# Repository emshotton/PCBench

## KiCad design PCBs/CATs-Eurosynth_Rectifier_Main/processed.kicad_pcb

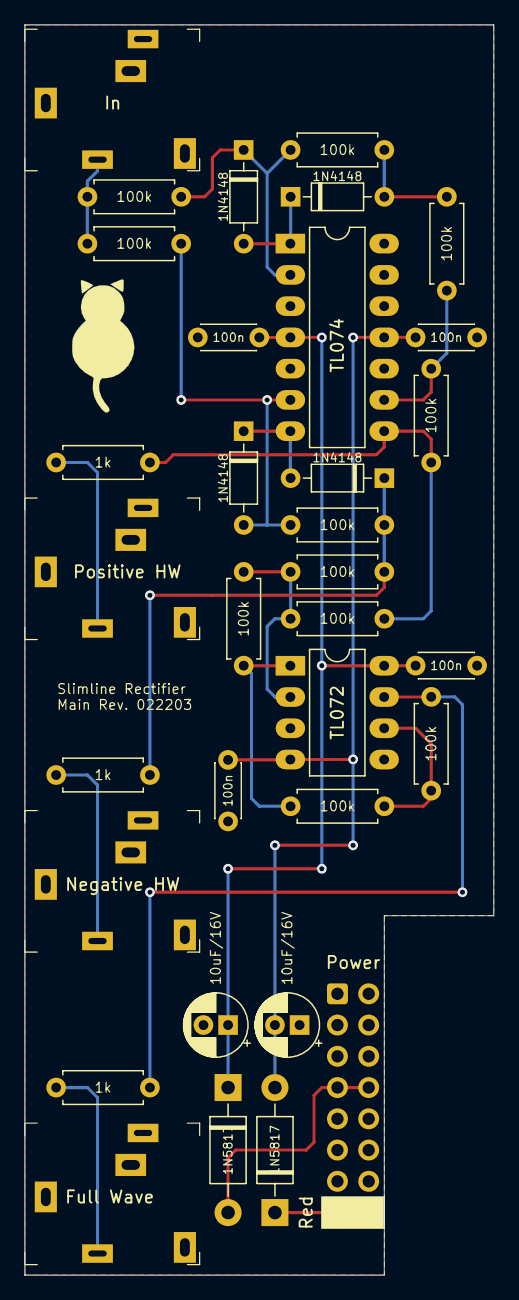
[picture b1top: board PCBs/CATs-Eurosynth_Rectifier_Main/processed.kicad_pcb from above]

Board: 2 copper layers, 38.1 x 101.6 mm, 33 parts (0 on the bottom side), 21 nets.

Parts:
C1, C4: 10uF/16V; CP_Radial_D5.0mm_P2.00mm
C2, C3, C5, C6: 100n; C_Disc_D4.3mm_W1.9mm_P5.00mm
D1, D2, D3, D4: 1N4148; D_DO-35_SOD27_P7.62mm_Horizontal
D5, D6: 1N5817; D_DO-41_SOD81_P10.16mm_Horizontal
J1: Negative HW; Jack_3.5mm_QingPu_WQP-PJ324M
J2: Full Wave; Jack_3.5mm_QingPu_WQP-PJ324M
J3: In; Jack_3.5mm_QingPu_WQP-PJ324M
J4: Positive HW; Jack_3.5mm_QingPu_WQP-PJ324M
J5: Power; Power_2x8_Horizontal
R1, R3, R4, R5, R6, R7, R8, R10, R11, R12, R13: 100k; R_Axial_DIN0207_L6.3mm_D2.5mm_P7.62mm_Horizontal
R2, R9, R14: 1k; R_Axial_DIN0207_L6.3mm_D2.5mm_P7.62mm_Horizontal
U1: TL074; DIP-14_W7.62mm_LongPads
U2: TL072; DIP-8_W7.62mm_LongPads

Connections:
+12V: C1.1, C2.1, C6.2, D5.1 (K), U1.4 (V+), U2.8 (V+)
-12V: C3.1, C4.2, C5.2, D6.2 (A), U1.11 (V-), U2.4 (V-)
GND: C1.2, C2.2, C3.2, C4.1, C5.1, C6.1, J1.S, J2.S, J3.S, J3.TN, J4.S, J5.GND, U1.3 (+), U1.5 (+), U1.10 (+), U2.3 (+), U2.5 (+)
unnamed: D1.1 (K), D2.2 (A), U1.7
unnamed: D1.2 (A), R1.1, R3.2, U1.6 (-)
unnamed: D2.1 (K), R1.2, R2.1, R5.1
unnamed: D3.1 (K), R10.1, R12.2, U1.2 (-)
unnamed: D3.2 (A), D4.1 (K), U1.1
unnamed: D4.2 (A), R10.2, R13.1
unnamed: D5.2 (A), J5.+12V
unnamed: D6.1 (K), J5.-12V
unnamed: J1.T, R2.2
unnamed: J2.T, R9.2
unnamed: J3.T, R3.1, R12.1
unnamed: J4.T, R14.2
unnamed: R4.1, R8.2, U2.6 (-)
unnamed: R4.2, R9.1, U2.7
unnamed: R5.2, R6.1, R7.2, U2.2 (-)
unnamed: R6.2, R8.1, U2.1
unnamed: R11.1, R13.2, U1.9 (-)
unnamed: R7.1, R11.2, R14.1, U1.8

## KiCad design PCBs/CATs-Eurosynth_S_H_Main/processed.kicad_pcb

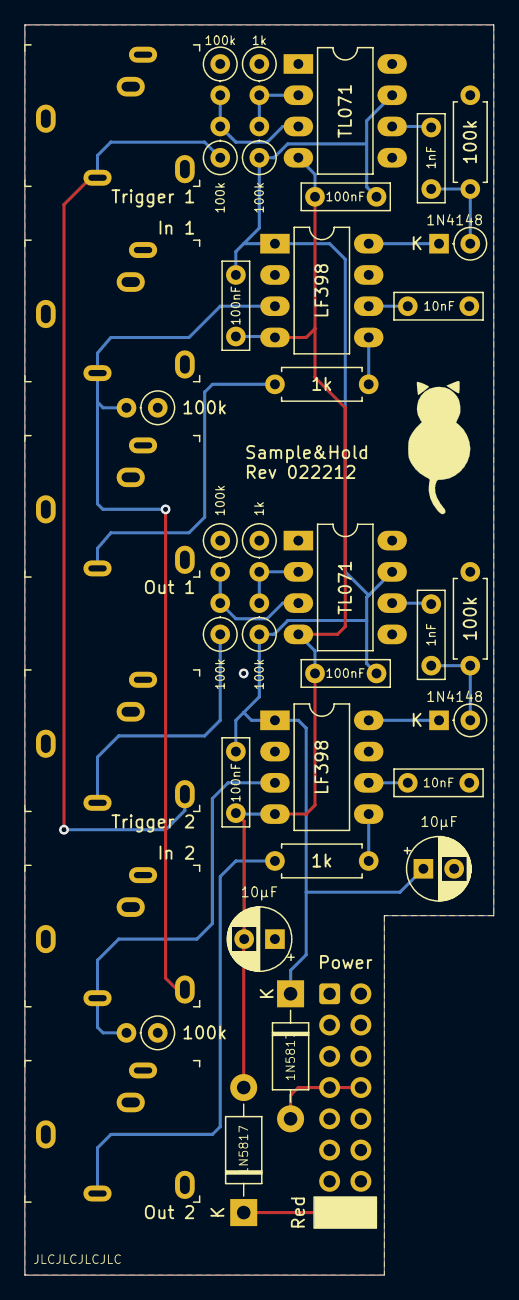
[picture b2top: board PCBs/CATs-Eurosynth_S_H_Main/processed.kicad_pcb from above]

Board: 2 copper layers, 38.1 x 101.6 mm, 39 parts (0 on the bottom side), 25 nets.

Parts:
C1, C2: 1nF; C_Rect_L7.0mm_W2.0mm_P5.00mm
C3, C8, C9, C10: 100nF; C_Rect_L7.0mm_W2.0mm_P5.00mm
C4, C5: 10µF; CP_Radial_D5.0mm_P2.50mm
C6, C7: 10nF; C_Rect_L7.0mm_W2.0mm_P5.00mm
D1, D2: 1N4148; D_DO-35_SOD27_P2.54mm_Vertical_KathodeUp
D3, D4: 1N5817; D_DO-41_SOD81_P10.16mm_Horizontal
J1: Trigger 2; PJ-324M-3
J2: In 2; PJ-324M-3
J3: Trigger 1; PJ-324M-3
J4: In 1; PJ-324M-3
J5: Power; Power_2x8_Horizontal
J6: Out 2; PJ-324M-3
J7: Out 1; PJ-324M-3
R1, R2, R3, R4, R5, R6, R7, R9: 100k; R_Axial_DIN0207_L6.3mm_D2.5mm_P2.54mm_Vertical
R8, R10: 1k; R_Axial_DIN0207_L6.3mm_D2.5mm_P2.54mm_Vertical
R11, R12: 100k; R_Axial_DIN0207_L6.3mm_D2.5mm_P7.62mm_Horizontal
R13, R14: 1k; R_Axial_DIN0207_L6.3mm_D2.5mm_P7.62mm_Horizontal
U1, U4: TL071; DIP-8_W7.62mm_LongPads
U2, U3: LF398; DIP-8_W7.62mm_LongPads

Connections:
+12V: C3.1, C4.1, C8.1, C9.1, C10.1, D3.1, R7.1, R9.1, U1.7, U2.1, U3.1, U4.7
-12V: C3.2, C5.2, C8.2, C9.2, C10.2, D4.2, U1.4, U2.4, U3.4, U4.4
GND: C4.2, C5.1, C6.2, C7.2, J1.S, J2.S, J3.S, J3.TN, J4.S, J4.TN, J5.GND, J6.S, J7.S, R1.1, R2.1, R5.1, R6.1, R8.1, R10.1, R11.1, R12.1, U2.7, U3.7
unnamed: C1.1, D1.2, R11.2
unnamed: C1.2, U1.6
unnamed: C2.1, D2.2, R12.2
unnamed: C2.2, U4.6
unnamed: C6.1, U2.6
unnamed: C7.1, U3.6
unnamed: D1.1, U2.8
unnamed: D2.1, U3.8
unnamed: D3.2, J5.+12V
unnamed: D4.1, J5.-12V
unnamed: J1.T, R3.1
unnamed: J1.TN, J3.T, R4.1
unnamed: J2.T, R1.2, U2.3
unnamed: J2.TN, J4.T, R2.2, U3.3
unnamed: J6.T, R13.1
unnamed: J7.T, R14.1
unnamed: R3.2, R5.2, U1.3
unnamed: R4.2, R6.2, U4.3
unnamed: R7.2, R8.2, U1.2
unnamed: R9.2, R10.2, U4.2
unnamed: R13.2, U2.5
unnamed: R14.2, U3.5

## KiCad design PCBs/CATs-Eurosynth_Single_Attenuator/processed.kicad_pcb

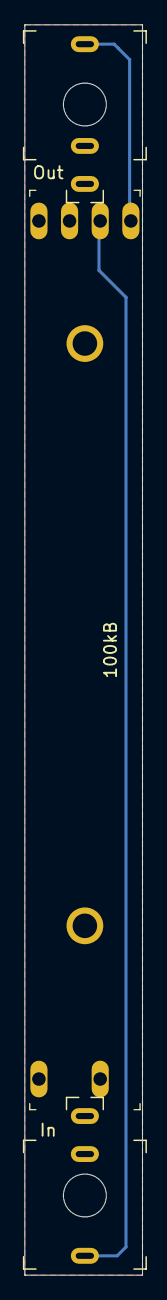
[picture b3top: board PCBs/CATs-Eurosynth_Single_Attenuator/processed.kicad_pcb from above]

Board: 2 copper layers, 9.6 x 102.0 mm, 3 parts (0 on the bottom side), 3 nets.

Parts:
J1: In; PJ-301-M-12
J2: Out; PJ-301-M-12
RV1: 100kB; Potentiometer_Fader_Alps_RS__01_Dual

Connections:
GND: J1.S, J1.TN, J2.S, RV1.3
unnamed: J1.T, RV1.1
unnamed: J2.T, RV1.2

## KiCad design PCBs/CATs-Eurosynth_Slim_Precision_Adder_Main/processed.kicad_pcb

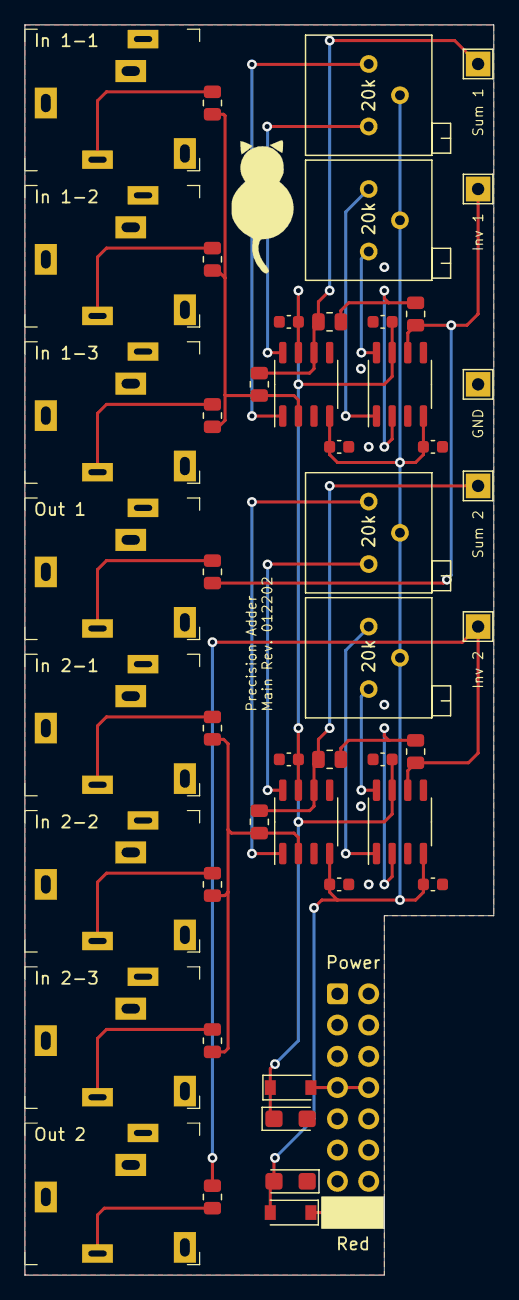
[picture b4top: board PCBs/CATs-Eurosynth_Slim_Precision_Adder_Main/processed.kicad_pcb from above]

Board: 2 copper layers, 38.1 x 101.6 mm, 48 parts (0 on the bottom side), 29 nets.

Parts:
C1, C6: 10u; CP_EIA-3216-18_Kemet-A
C2, C3, C4, C5, C7, C8, C9, C10: 100n; C_0603_1608Metric
D1, D2: B5819W SL; D_SOD-123
J1: In 1-1; Jack_3.5mm_QingPu_WQP-PJ324M
J2: Out 1; Jack_3.5mm_QingPu_WQP-PJ324M
J3: In 1-2; Jack_3.5mm_QingPu_WQP-PJ324M
J4: In 1-3; Jack_3.5mm_QingPu_WQP-PJ324M
J5: In 2-1; Jack_3.5mm_QingPu_WQP-PJ324M
J6: Out 2; Jack_3.5mm_QingPu_WQP-PJ324M
J7: In 2-2; Jack_3.5mm_QingPu_WQP-PJ324M
J8: In 2-3; Jack_3.5mm_QingPu_WQP-PJ324M
J9: Power; Power_2x8_Horizontal
R1, R2, R3, R5, R6, R7, R8, R9, R10, R12, R13, R14: 100k ±0.05%; R_0805_2012Metric
R4, R11: 240; R_0805_2012Metric
RV1, RV2, RV3, RV4: 20k; Potentiometer_Bourns_3299P_Horizontal
TP1: Inv 1; TestPoint_THTPad_2.0x2.0mm_Drill1.0mm
TP2: Sum 1; TestPoint_THTPad_2.0x2.0mm_Drill1.0mm
TP3: GND; TestPoint_THTPad_2.0x2.0mm_Drill1.0mm
TP4: Inv 2; TestPoint_THTPad_2.0x2.0mm_Drill1.0mm
TP5: Sum 2; TestPoint_THTPad_2.0x2.0mm_Drill1.0mm
U1, U2, U3, U4: OP07CDR; SO-8_3.9x4.9mm_P1.27mm

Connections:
+12V: C1.1, C2.1, C3.1, C4.1, C5.1, D1.1, U1.7, U2.7, U3.7, U4.7
-12V: C6.2, C7.2, C8.2, C9.2, C10.2, D2.2, RV1.2, RV2.2, RV3.2, RV4.2, U1.4, U2.4, U3.4, U4.4
GND: C1.2, C2.2, C3.2, C4.2, C5.2, C6.1, C7.1, C8.1, C9.1, C10.1, J1.S, J1.TN, J2.S, J3.S, J3.TN, J4.S, J4.TN, J5.S, J5.TN, J6.S, J7.S, J7.TN, J8.S, J8.TN, J9.GND, TP3.1, U1.3, U2.3, U3.3, U4.3
unnamed: D1.2, J9.+12V
unnamed: D2.1, J9.-12V
unnamed: J1.T, R3.2
unnamed: J2.T, R4.1
unnamed: J3.T, R6.2
unnamed: J4.T, R7.2
unnamed: J5.T, R10.2
unnamed: J6.T, R11.1
unnamed: J7.T, R13.2
unnamed: J8.T, R14.2
unnamed: R1.1, R4.2, TP1.1, U1.6
unnamed: R1.2, R5.1, U1.2
unnamed: R2.1, R5.2, TP2.1, U2.6
unnamed: R2.2, R3.1, R6.1, R7.1, U2.2
unnamed: R9.2, R10.1, R13.1, R14.1, U4.2
unnamed: R8.1, R11.2, TP4.1, U3.6
unnamed: R8.2, R12.1, U3.2
unnamed: R9.1, R12.2, TP5.1, U4.6
unnamed: RV1.1, U1.8
unnamed: RV1.3, U1.1
unnamed: RV2.1, U2.8
unnamed: RV2.3, U2.1
unnamed: RV3.1, U3.8
unnamed: RV3.3, U3.1
unnamed: RV4.1, U4.8
unnamed: RV4.3, U4.1

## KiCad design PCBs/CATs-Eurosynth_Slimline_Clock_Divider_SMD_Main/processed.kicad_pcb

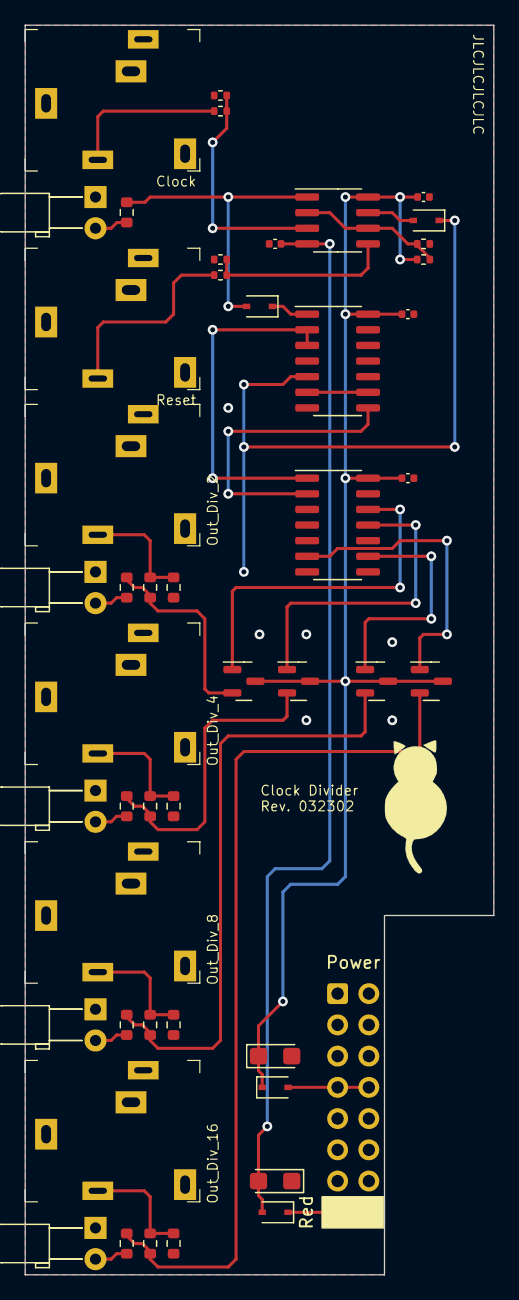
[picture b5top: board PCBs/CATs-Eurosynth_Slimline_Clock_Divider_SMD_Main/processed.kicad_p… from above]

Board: 2 copper layers, 38.1 x 101.6 mm, 48 parts (0 on the bottom side), 34 nets.

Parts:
C1, C4, C5, C6: 100nF; C_0402_1005Metric
C2, C3: 10uF/16V; CP_EIA-3216-18_Kemet-A
D1, D5, D6, D7, D8: LED; LED_D3.0mm_Horizontal_O3.81mm_Z6.0mm
D2, D4: 1N5819WS; D_SOD-323
D3, D9: 1N4148WS; D_SOD-323
IC1: TL072CDT; SOIC-8_3.9x4.9mm_P1.27mm
IC3: CD4069UBM96; SOIC-14_3.9x8.7mm_P1.27mm
IC4: CD4024BM96; SOIC-14_3.9x8.7mm_P1.27mm
J1: Clock; Jack_3.5mm_QingPu_WQP-PJ324M
J2: Out_Div_2; Jack_3.5mm_QingPu_WQP-PJ324M
J3: Out_Div_4; Jack_3.5mm_QingPu_WQP-PJ324M
J4: Reset; Jack_3.5mm_QingPu_WQP-PJ324M
J5: Out_Div_8; Jack_3.5mm_QingPu_WQP-PJ324M
J6: Out_Div_16; Jack_3.5mm_QingPu_WQP-PJ324M
J7: Power_2x5; Power_2x8_Horizontal
Q1, Q2, Q3, Q4: MMBT3904; SOT-23
R1, R2, R5: 100k; R_0402_1005Metric
R4, R10, R15: 10k; R_0402_1005Metric
R7, R14, R17, R19: 1k2; R_0603_1608Metric
R8, R12, R16, R18, R20, R21, R22, R23, R24: 1k; R_0603_1608Metric

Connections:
+12V: C1.1, C2.1, C4.1, C5.1, D2.1 (K), IC1.8 (V+), IC3.14 (VCC), IC4.14 (VCC), Q1.3 (C), Q2.3 (C), Q3.3 (C), Q4.3 (C), R1.2
-12V: C3.2, C6.2, D4.2 (A), IC1.4 (V-)
GND: C1.2, C2.2, C3.1, C4.2, C5.2, C6.1, D1.1 (K), D5.1 (K), D6.1 (K), D7.1 (K), D8.1 (K), IC3.7 (GND), IC4.7 (GND), J1.S, J1.TN, J2.S, J3.S, J4.S, J4.TN, J5.S, J6.S, J7.GND, R2.1, R5.1, R8.2, R15.1, R16.2, R18.2, R20.2
L/2: Q1.2 (E), R7.1, R21.1
L/4: Q2.2 (E), R14.1, R22.1
L/8: Q3.2 (E), R17.1, R23.1
L/16: Q4.2 (E), R19.1, R24.1
unnamed: D1.2 (A), R12.2
unnamed: D2.2 (A), J7.+12V
unnamed: D4.1 (K), J7.-12V
unnamed: D5.2 (A), R21.2
unnamed: D6.2 (A), R22.2
unnamed: D7.2 (A), R23.2
unnamed: D8.2 (A), R24.2
unnamed: D3.2 (A), IC1.1, R12.1
unnamed: IC1.2 (-), IC1.6 (-), R1.1, R15.2
unnamed: IC1.3 (+), R2.2, R4.2
unnamed: IC1.5 (+), R5.2, R10.2
unnamed: D9.2 (A), IC1.7
unnamed: D3.1 (K), IC3.1
unnamed: IC3.2, IC4.1 (~CP)
unnamed: D9.1 (K), IC3.5
unnamed: IC3.6, IC3.9
unnamed: IC3.8, IC4.2 (MR)
unnamed: IC4.6 (Q3), Q4.1 (B)
unnamed: IC4.9 (Q2), Q3.1 (B)
unnamed: IC4.11 (Q1), Q2.1 (B)
unnamed: IC4.12 (Q0), Q1.1 (B)
unnamed: J1.T, R4.1
unnamed: J2.T, R7.2, R8.1
unnamed: J3.T, R14.2, R16.1
unnamed: J4.T, R10.1
unnamed: J5.T, R17.2, R18.1
unnamed: J6.T, R19.2, R20.1

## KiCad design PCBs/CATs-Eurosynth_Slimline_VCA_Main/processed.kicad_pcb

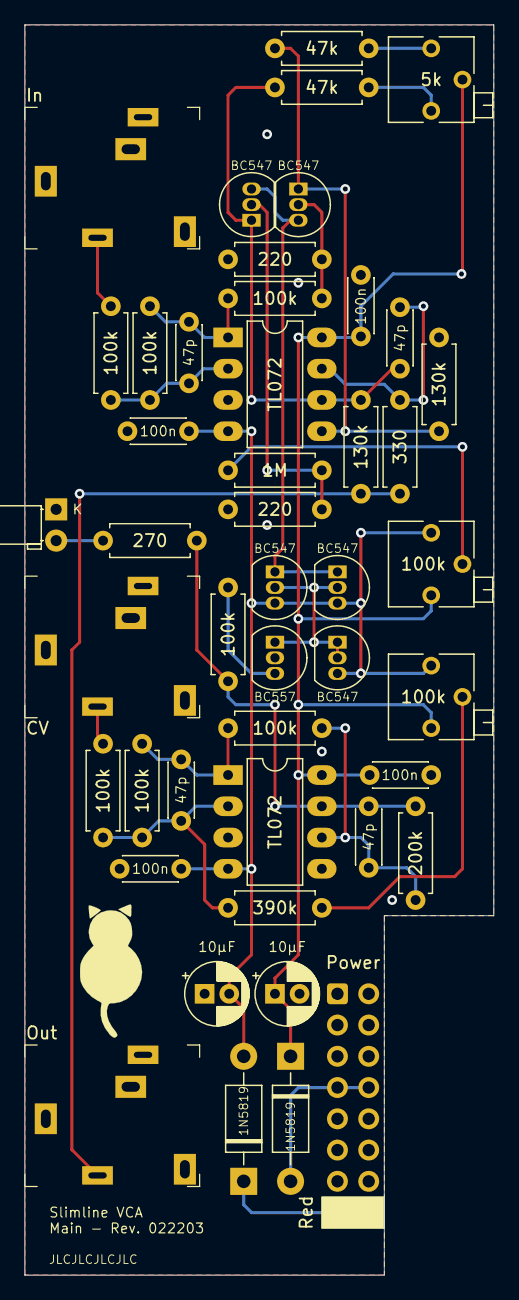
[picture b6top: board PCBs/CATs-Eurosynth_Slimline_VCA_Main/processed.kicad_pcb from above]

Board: 2 copper layers, 38.1 x 101.6 mm, 46 parts (0 on the bottom side), 27 nets.

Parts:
C1, C2, C3, C4: 47p; C_Disc_D4.3mm_W1.9mm_P5.00mm
C5, C6: 10µF; CP_Radial_D5.0mm_P2.00mm
C7, C8, C9, C10: 100n; C_Disc_D4.3mm_W1.9mm_P5.00mm
D1, D2: 1N5819; D_DO-41_SOD81_P10.16mm_Horizontal
D3: LED; LED_D3.0mm_Horizontal_O1.27mm_Z2.0mm
J1: CV; Jack_3.5mm_QingPu_WQP-PJ324M
J2: In; Jack_3.5mm_QingPu_WQP-PJ324M
J3: Out; Jack_3.5mm_QingPu_WQP-PJ324M
J4: Power; Power_2x8_Horizontal
Q1: BC557; TO-92_Inline
Q2, Q3, Q4, Q5, Q6: BC547; TO-92_Inline
R1: 390k; R_Axial_DIN0207_L6.3mm_D2.5mm_P7.62mm_Horizontal
R2, R3, R4, R6, R7, R8, R9: 100k; R_Axial_DIN0207_L6.3mm_D2.5mm_P7.62mm_Horizontal
R5: 200k; R_Axial_DIN0207_L6.3mm_D2.5mm_P7.62mm_Horizontal
R10, R13: 220; R_Axial_DIN0207_L6.3mm_D2.5mm_P7.62mm_Horizontal
R11, R12: 47k; R_Axial_DIN0207_L6.3mm_D2.5mm_P7.62mm_Horizontal
R14: 1M; R_Axial_DIN0207_L6.3mm_D2.5mm_P7.62mm_Horizontal
R15, R16: 130k; R_Axial_DIN0207_L6.3mm_D2.5mm_P7.62mm_Horizontal
R17: 330; R_Axial_DIN0207_L6.3mm_D2.5mm_P7.62mm_Horizontal
R18: 270; R_Axial_DIN0207_L6.3mm_D2.5mm_P7.62mm_Horizontal
RV1, RV3: 100k; Potentiometer_Bourns_3266P_Horizontal
RV2: 5k; Potentiometer_Bourns_3266P_Horizontal
U1, U2: TL072; DIP-8_W7.62mm_LongPads

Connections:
+12V: C5.1, C7.2, C9.2, D1.1, RV1.1, RV2.2, RV3.1, U1.8, U2.8
-12V: C6.2, C8.1, C10.1, D2.2, Q2.3, Q4.3, Q5.3, RV1.3, RV3.3, U1.4, U2.4
GND: C5.2, C6.1, C7.1, C8.2, C9.1, C10.2, D3.1, J1.S, J1.TN, J2.S, J2.TN, J3.S, J4.GND, Q1.2, R10.2, R13.2, R15.2, U1.3, U2.3, U2.5
unnamed: C1.1, R3.1, R4.2, U2.1
unnamed: C1.2, R1.1, R2.1, R3.2, U2.2
unnamed: C2.1, R5.1, R6.2, R18.2, U2.7
unnamed: C2.2, R4.1, R5.2, U2.6
unnamed: C3.1, R8.1, R9.2, U1.1
unnamed: C3.2, R7.1, R8.2, U1.2
unnamed: C4.1, R17.2, U1.7
unnamed: C4.2, Q6.1, R12.2, R16.2, U1.6
unnamed: D1.2, J4.+12V
unnamed: D2.1, J4.-12V
unnamed: D3.2, R18.1
unnamed: J1.T, R2.2
unnamed: J2.T, R7.2
unnamed: J3.T, R16.1, R17.1
unnamed: Q1.1, Q2.1, Q2.2, Q4.2, Q5.2
unnamed: Q1.3, R6.1
unnamed: Q3.1, R11.2, R15.1, U1.5
unnamed: Q3.2, R9.1, R10.1
unnamed: Q3.3, Q4.1, Q5.1, Q6.3
unnamed: Q6.2, R13.1, R14.2
unnamed: R1.2, RV1.2
unnamed: R11.1, RV2.3
unnamed: R12.1, RV2.1
unnamed: R14.1, RV3.2

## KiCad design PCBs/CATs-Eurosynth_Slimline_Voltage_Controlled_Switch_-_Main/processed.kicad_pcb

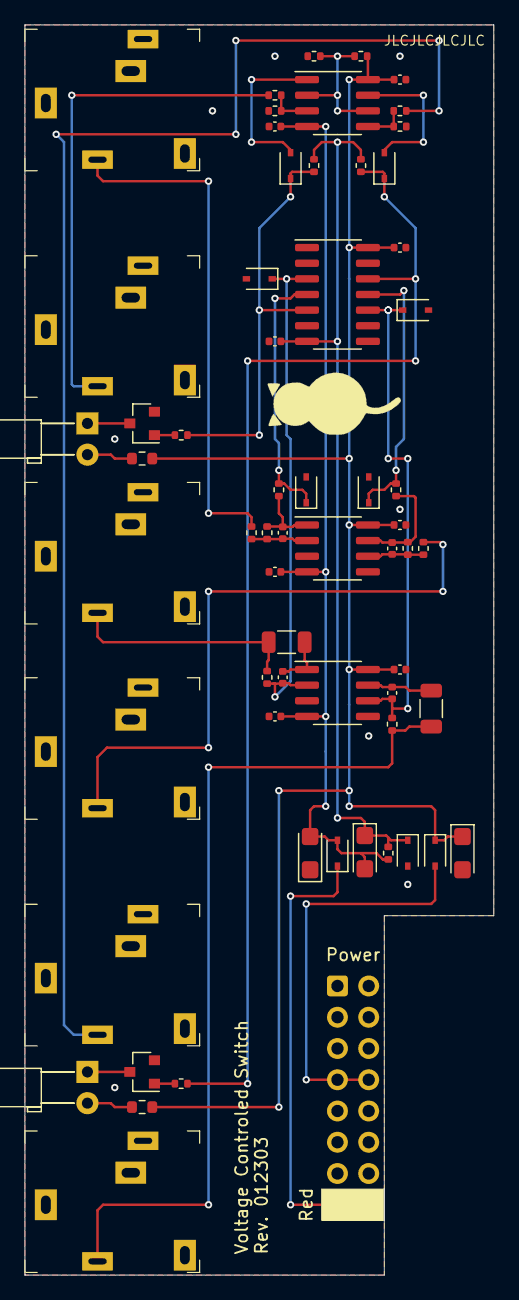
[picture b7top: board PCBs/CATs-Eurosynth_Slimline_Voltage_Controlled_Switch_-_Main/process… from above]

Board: 2 copper layers, 38.1 x 101.6 mm, 62 parts (0 on the bottom side), 35 nets.

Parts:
C1, C2, C3, C4: 47p; C_0402_1005Metric
C5, C10, C12: 10µF; CP_EIA-3216-18_Kemet-A
C6, C7, C8, C9, C11, C13, C14, C15: 100n; C_0402_1005Metric
D1, D2, D3, D4, D6, D8, D10: 1N4148WS; D_SOD-323
D5, D7: LED; LED_D3.0mm_Horizontal_O3.81mm_Z6.0mm
D9, D11: 1N5817WS; D_SOD-323
J1: IN 1; Jack_3.5mm_QingPu_WQP-PJ324M
J2: OUT 1; Jack_3.5mm_QingPu_WQP-PJ324M
J3: IN 2; Jack_3.5mm_QingPu_WQP-PJ324M
J4: OUT 2; Jack_3.5mm_QingPu_WQP-PJ324M
J5: Switch 1; Jack_3.5mm_QingPu_WQP-PJ324M
J6: Switch 2; Jack_3.5mm_QingPu_WQP-PJ324M
J7: Power; Power_2x8_Horizontal
Q1, Q2: MMBT3904; SOT-23
R1, R2, R3, R4, R6, R7, R8, R9, R12, R14, R15, R16, R21, R22, R23: 100k; R_0402_1005Metric
R5, R10: 1k; R_1206_3216Metric
R11, R18: 1k; R_0603_1608Metric
R13, R17, R20: 10k; R_0402_1005Metric
R24: 1k; R_0402_1005Metric
U1, U3, U4: TL072CDT; SOIC-8_3.9x4.9mm_P1.27mm
U2: CD4066BM/TR; SOIC-14_3.9x8.7mm_P1.27mm

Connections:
+12V: C5.1, C6.2, C7.2, C8.2, C11.2, D9.1, R11.1, R12.2, R18.1, U1.8, U2.14, U3.8, U4.8
-12V: C10.2, C12.2, C13.1, C14.1, C15.1, D11.2, R17.1, U1.4, U3.4, U4.4
B1: D6.1, R14.1, R16.2, U2.5
B2: D8.1, R21.1, R23.2, U2.12
GND: C5.2, C6.1, C7.1, C8.1, C9.2, C11.1, C12.1, C13.2, C14.2, C15.2, D1.2, D2.2, D3.2, D4.2, D10.2, J1.S, J1.TN, J2.S, J3.S, J3.TN, J4.S, J5.S, J5.TN, J6.S, J6.TN, J7.GND, Q1.2, Q2.2, R15.1, R22.1, R24.2, U1.3, U1.5, U3.3, U3.5
unnamed: C1.1, R2.1, R4.2, U1.1
unnamed: C1.2, R2.2, R3.1, U1.2
unnamed: C2.1, R5.2, U3.1
unnamed: C2.2, D2.1, R1.2, U2.3, U3.2
unnamed: C3.1, R7.1, R9.2, U1.7
unnamed: C3.2, R7.2, R8.1, U1.6
unnamed: C4.1, R10.2, U3.7
unnamed: C4.2, D4.1, R6.2, U2.10, U3.6
unnamed: D1.1, R4.1, U2.4
unnamed: D3.1, R9.1, U2.11
unnamed: D5.1, Q1.3
unnamed: D5.2, R11.2
unnamed: D6.2, U4.1
unnamed: D7.1, Q2.3
unnamed: D7.2, R18.2
unnamed: D8.2, U4.7
unnamed: D9.2, J7.+12V
unnamed: D11.1, J7.-12V
unnamed: J1.T, R3.2
unnamed: J2.T, R1.1, R5.1
unnamed: J3.T, R8.2
unnamed: J4.T, R6.1, R10.1
unnamed: J5.T, R13.2
unnamed: J6.T, R20.2
unnamed: Q1.1, R14.2
unnamed: Q2.1, R21.2
unnamed: R12.1, R24.1, U4.2, U4.6
unnamed: R13.1, R15.2, U4.3
unnamed: R20.1, R22.2, U4.5
VEE: C9.1, C10.1, D10.1, R16.1, R17.2, R23.1, U2.7
